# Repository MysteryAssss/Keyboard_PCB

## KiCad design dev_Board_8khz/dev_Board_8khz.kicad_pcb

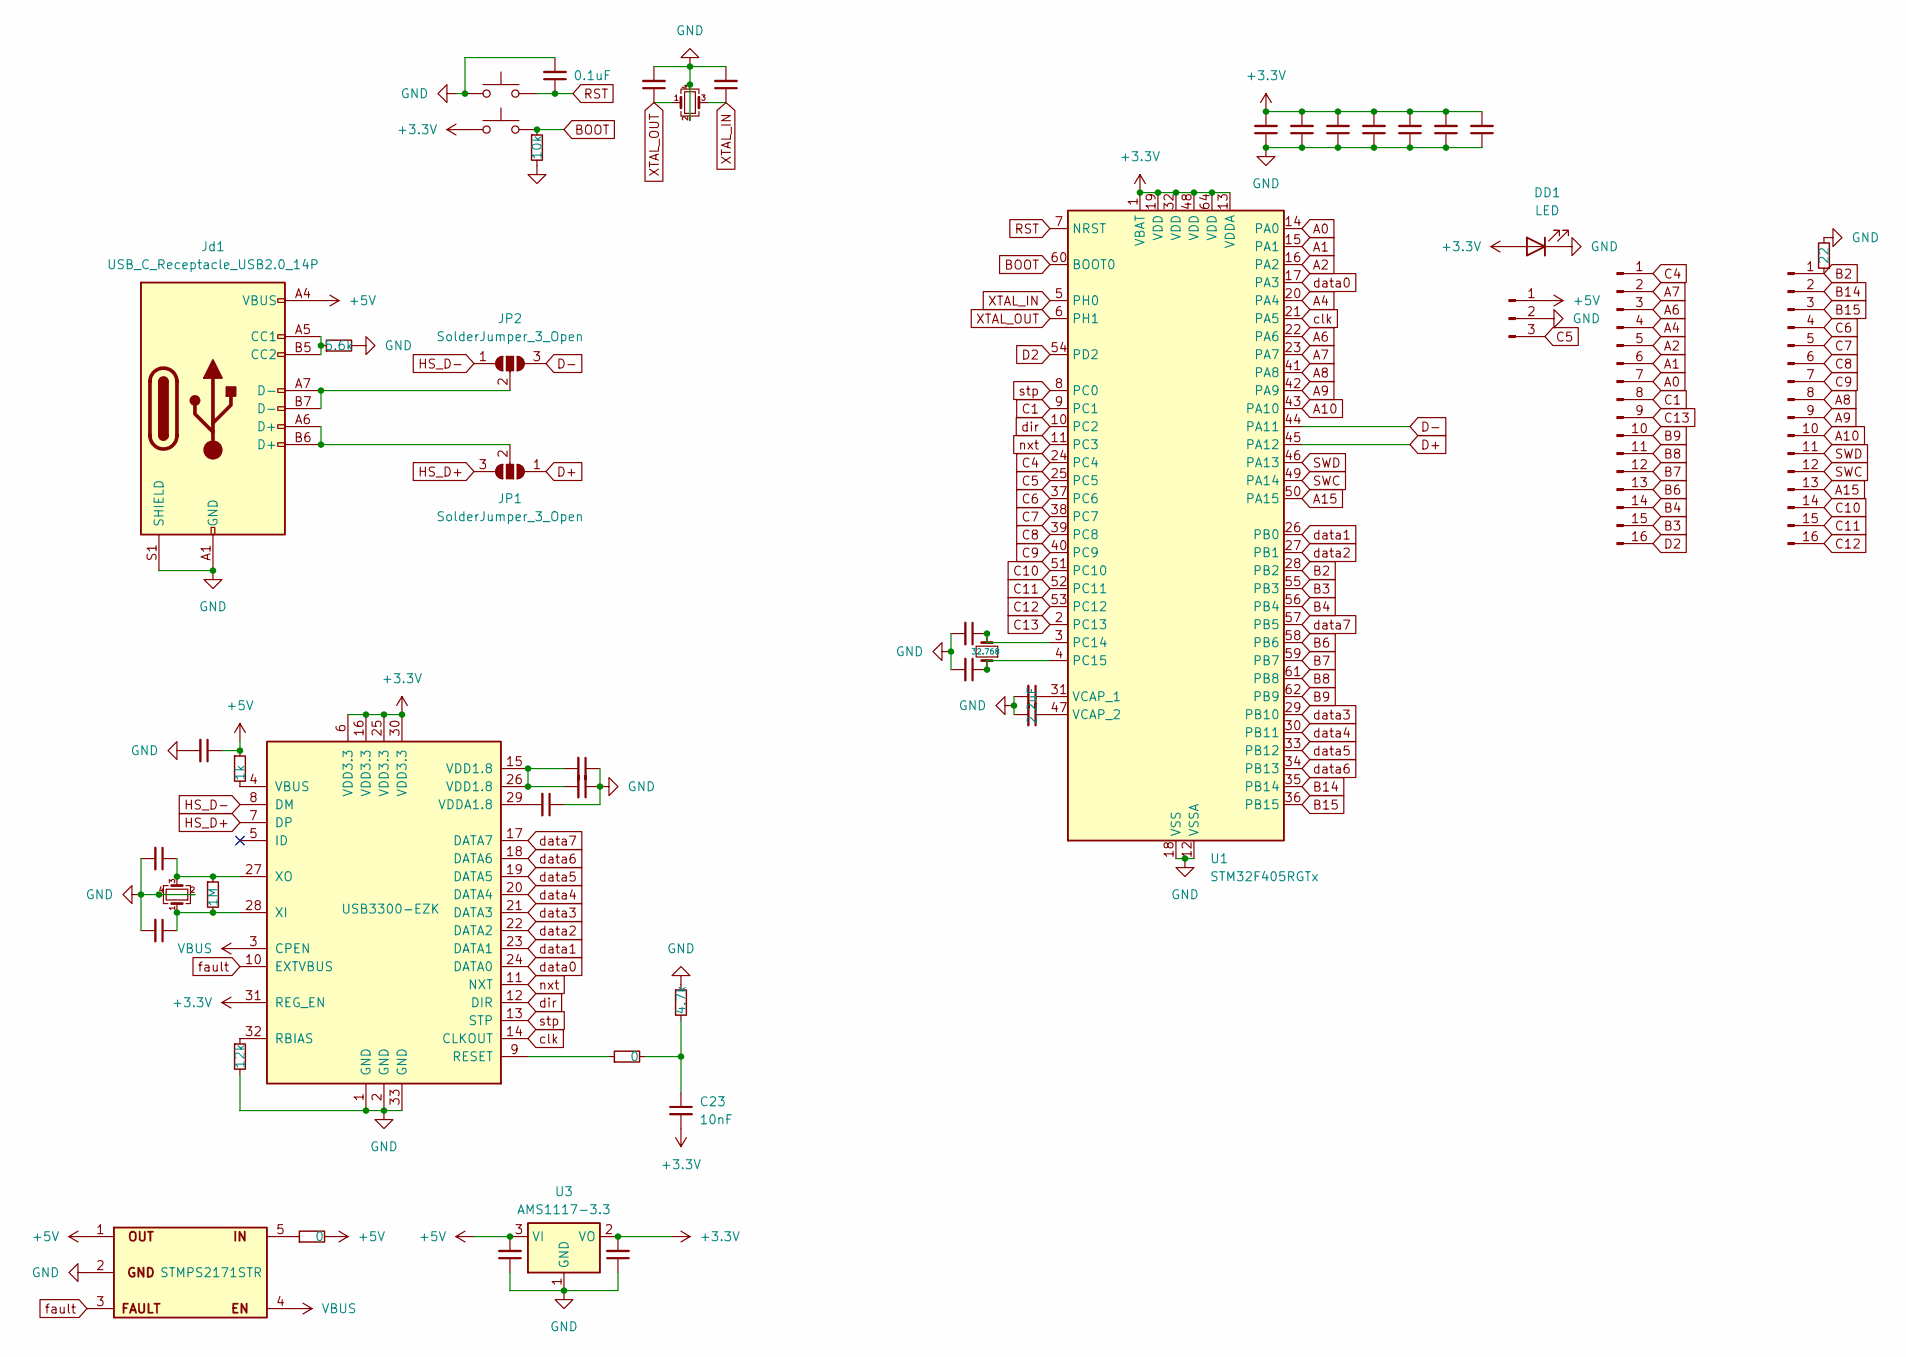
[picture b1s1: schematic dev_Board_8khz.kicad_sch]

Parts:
BOOT0: SW_Push; JST_EH_B2B-EH-A_1x02_P2.50mm_Vertical
C1: 0.1uF; C_0603_1608Metric
C2, C3: 2.2uF; C_0603_1608Metric
C4, C5, C6, C7, C8, C12, C13, C14, C15: 12pF; C_0603_1608Metric
C9, C11: 4.7uF; C_0603_1608Metric
C10: 1uF; C_0603_1608Metric
C16, C17, C18, C19, C20, C21, C22: 0.1Uf; C_0603_1608Metric
C23: 10nF; C_0603_1608Metric
DD1: LED; LED_PLCC-2_3.4x3.0mm_KA
J1: Conn_01x03_Pin; JST_EH_B3B-EH-A_1x03_P2.50mm_Vertical
J2, J3: Conn_01x16_Pin; PinHeader_1x16_P2.54mm_Vertical
J4: STMPS2171STR; SOT-23-5
JP1, JP2: SolderJumper_3_Open; SolderJumper-3_P1.3mm_Open_RoundedPad1.0x1.5mm
Jd1: USB_C_Receptacle_USB2.0_14P; USB_C_Receptacle_G-Switch_GT-USB-7010ASV
R1: 10k; R_0603_1608Metric
R2: 12k; R_0603_1608Metric
R3: 1M; R_0603_1608Metric
R4: 1k; R_0603_1608Metric
R5: 5.6k; R_0603_1608Metric
R6, R10: 0; R_0603_1608Metric
R8: 22; R_0603_1608Metric
R9: 4.7k; R_0603_1608Metric
RST1: SW_Push; JST_EH_B2B-EH-A_1x02_P2.50mm_Vertical
U1: STM32F405RGTx; LQFP-64_10x10mm_P0.5mm
U2: USB3300-EZK; QFN-32-1EP_5x5mm_P0.5mm_EP3.45x3.45mm
U3: AMS1117-3.3; SOT-223-3_TabPin2
Y1: 12mhz; Crystal_SMD_3225-4Pin_3.2x2.5mm
Y2: 24mhz; Crystal_SMD_3225-4Pin_3.2x2.5mm
Y3: 32.768; Crystal_SMD_3215-2Pin_3.2x1.5mm

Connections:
+3.3V: BOOT0.1, C13.2, C16.2, C17.2, C18.2, C19.2, C20.2, C21.2, C22.2, C23.2, DD1.2 (A), U1.1 (VBAT), U1.13 (VDDA), U1.19 (VDD), U1.32 (VDD), U1.48 (VDD), U1.64 (VDD), U2.6 (VDD3.3), U2.16 (VDD3.3), U2.25 (VDD3.3), U2.30 (VDD3.3), U2.31 (REG_EN), U3.2 (VO)
+5V: C8.1, C12.2, J1.1, J4.1, Jd1.A4 (VBUS), Jd1.A9 (VBUS), Jd1.B4 (VBUS), Jd1.B9 (VBUS), R4.1, R6.2, U3.3 (VI)
A0: J2.7, U1.14 (PA0)
A1: J2.6, U1.15 (PA1)
A2: J2.5, U1.16 (PA2)
A4: J2.4, U1.20 (PA4)
A6: J2.3, U1.22 (PA6)
A7: J2.2, U1.23 (PA7)
A8: J3.8, U1.41 (PA8)
A9: J3.9, U1.42 (PA9)
A10: J3.10, U1.43 (PA10)
A15: J3.13, U1.50 (PA15)
B2: J3.1, R8.1, U1.28 (PB2)
B3: J2.15, U1.55 (PB3)
B4: J2.14, U1.56 (PB4)
B6: J2.13, U1.58 (PB6)
B7: J2.12, U1.59 (PB7)
B8: J2.11, U1.61 (PB8)
B9: J2.10, U1.62 (PB9)
B14: J3.2, U1.35 (PB14)
B15: J3.3, U1.36 (PB15)
BOOT: BOOT0.2, R1.1, U1.60 (BOOT0)
C1: J2.8, U1.9 (PC1)
C4: J2.1, U1.24 (PC4)
C5: J1.3, U1.25 (PC5)
C6: J3.4, U1.37 (PC6)
C7: J3.5, U1.38 (PC7)
C8: J3.6, U1.39 (PC8)
C9: J3.7, U1.40 (PC9)
C10: J3.14, U1.51 (PC10)
C11: J3.15, U1.52 (PC11)
C12: J3.16, U1.53 (PC12)
C13: J2.9, U1.2 (PC13)
D2: J2.16, U1.54 (PD2)
D+: JP1.1 (A), U1.45 (PA12)
D-: JP2.3 (B), U1.44 (PA11)
GND: C1.2, C2.2, C3.2, C4.2, C5.2, C6.2, C7.2, C8.2, C9.1, C10.1, C11.1, C12.1, C13.1, C14.2, C15.2, C16.1, C17.1, C18.1, C19.1, C20.1, C21.1, C22.1, DD1.1 (K), J1.2, J4.2, Jd1.A1 (GND), Jd1.A12 (GND), Jd1.B1 (GND), Jd1.B12 (GND), Jd1.S1 (SHIELD), R1.2, R2.2, R5.2, R8.2, R9.1, RST1.1, U1.12 (VSSA), U1.18 (VSS), U1.63 (VSS), U2.1 (GND), U2.2 (GND), U2.33 (GND), U3.1 (GND), Y1.2, Y1.4, Y2.2, Y2.4
HS_D+: JP1.3 (B), U2.7 (DP)
HS_D-: JP2.1 (A), U2.8 (DM)
unnamed: C9.2, C10.2, U2.15 (VDD1.8), U2.26 (VDD1.8)
unnamed: C23.1, R9.2, R10.2
unnamed: J4.5, R6.1
unnamed: JP1.2 (C), Jd1.A6 (D+), Jd1.B6 (D+)
unnamed: JP2.2 (C), Jd1.A7 (D-), Jd1.B7 (D-)
unnamed: Jd1.A5 (CC1), Jd1.B5 (CC2), R5.1
unnamed: C15.1, U1.3 (PC14), Y3.2
unnamed: C14.1, U1.4 (PC15), Y3.1
unnamed: C2.1, U1.31 (VCAP_1)
unnamed: C3.1, U1.47 (VCAP_2)
unnamed: R2.1, U2.32 (RBIAS)
unnamed: R10.1, U2.9 (RESET)
unnamed: R4.2, U2.4 (VBUS)
unnamed: C11.2, U2.29 (VDDA1.8)
unnamed: C6.1, R3.2, U2.28 (XI), Y2.1
unnamed: C7.1, R3.1, U2.27 (XO), Y2.3
RST: C1.1, RST1.2, U1.7 (NRST)
SWC: J3.12, U1.49 (PA14)
SWD: J3.11, U1.46 (PA13)
VBUS: J4.4, U2.3 (CPEN)
XTAL_IN: C5.1, U1.5 (PH0), Y1.3
XTAL_OUT: C4.1, U1.6 (PH1), Y1.1
clk: U1.21 (PA5), U2.14 (CLKOUT)
data0: U1.17 (PA3), U2.24 (DATA0)
data1: U1.26 (PB0), U2.23 (DATA1)
data2: U1.27 (PB1), U2.22 (DATA2)
data3: U1.29 (PB10), U2.21 (DATA3)
data4: U1.30 (PB11), U2.20 (DATA4)
data5: U1.33 (PB12), U2.19 (DATA5)
data6: U1.34 (PB13), U2.18 (DATA6)
data7: U1.57 (PB5), U2.17 (DATA7)
dir: U1.10 (PC2), U2.12 (DIR)
fault: J4.3, U2.10 (EXTVBUS)
nxt: U1.11 (PC3), U2.11 (NXT)
stp: U1.8 (PC0), U2.13 (STP)

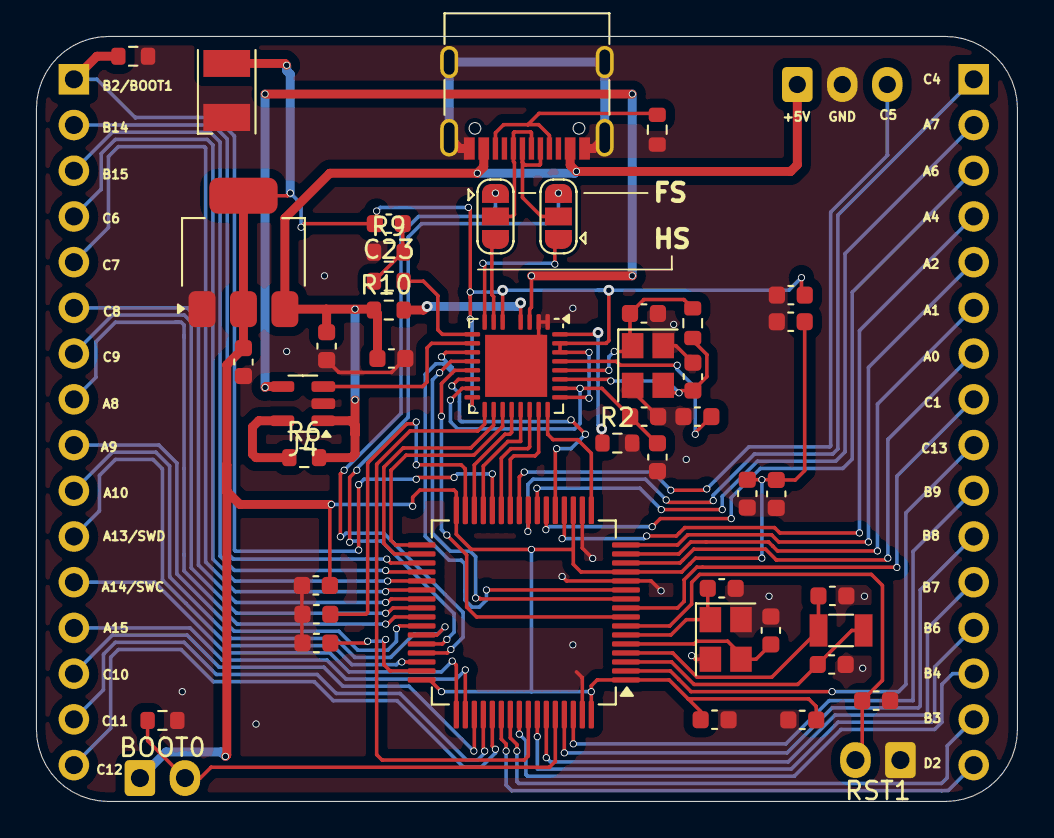
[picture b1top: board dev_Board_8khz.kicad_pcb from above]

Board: 2 copper layers, 54.5 x 42.5 mm, 48 parts (0 on the bottom side), 74 nets.

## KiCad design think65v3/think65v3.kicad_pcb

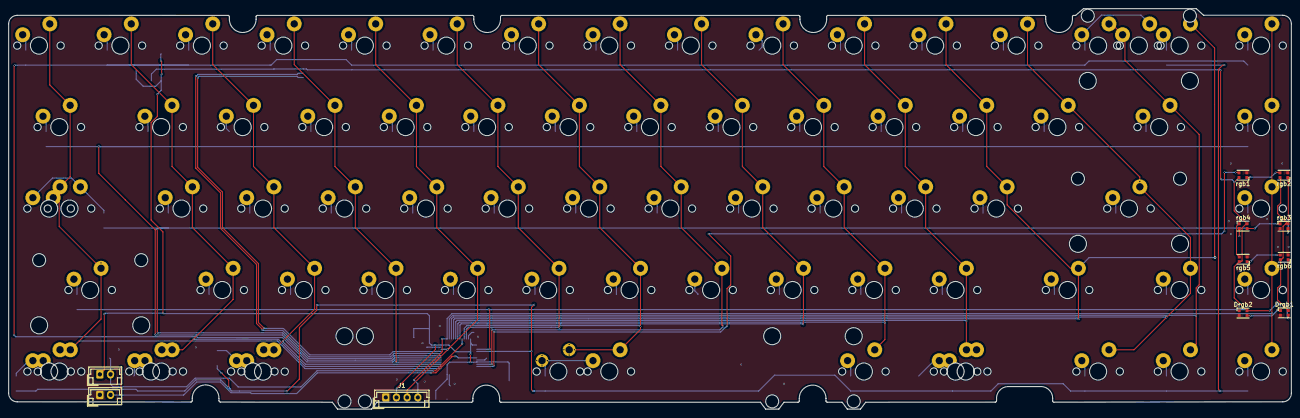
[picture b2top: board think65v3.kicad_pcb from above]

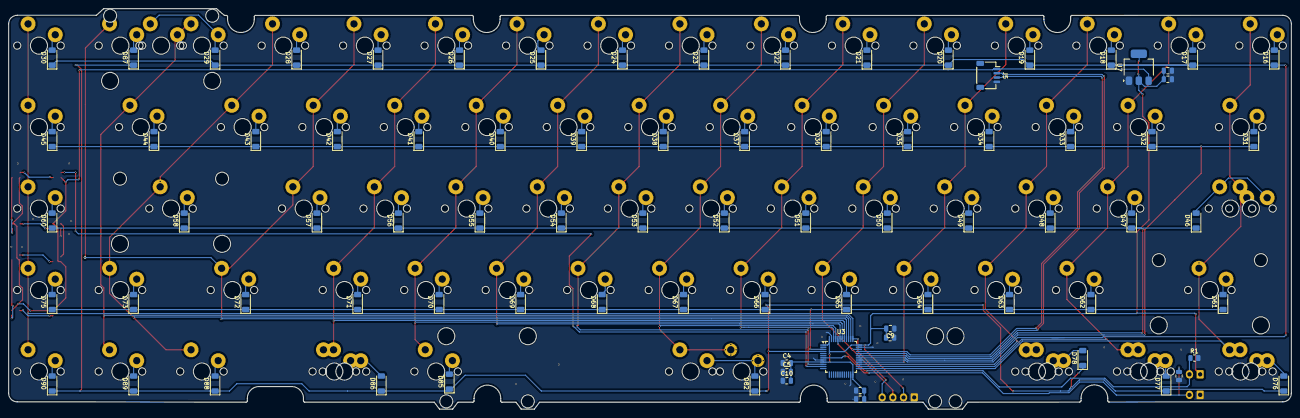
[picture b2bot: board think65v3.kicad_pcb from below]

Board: 2 copper layers, 299.9 x 93.6 mm, 168 parts (82 on the bottom side), 103 nets.

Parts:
C1, C2, C4, C5, C8, C10: 4.7uF; C_0805_2012Metric
C3, C6, C7, C9: 100nF; C_0805_2012Metric
D16, D17, D18, D19, D20, D21, D22, D23, D24, D25, D26, D27, D28, D29, D30, D31, D32, D33, D34, D35, D36, D37, D38, D39, D40, D41, D42, D43, D44, D45, D46, D47, D48, D49, D50, D51, D52, D53, D54, D55, D56, D57, D58, D60, D61, D62, D63, D64, D65, D66, D67, D68, D69, D70, D71, D72, D73, D75, D76, D77, D78, D82, D85, D86, D87, D88, D89, D90: D_Small; D_MiniMELF
Drgb1, Drgb2: WS2812B-2020; LED_WS2812B-2020_PLCC4_2.0x2.0mm
J1: Conn_01x04_Pin; JST_EH_B4B-EH-A_1x04_P2.50mm_Vertical
J5: Conn_01x04_Pin; JST_SH_SM04B-SRSS-TB_1x04-1MP_P1.00mm_Horizontal
R1: R_Small; R_0805_2012Metric
SW16, SW17, SW18, SW19, SW20, SW21, SW22, SW23, SW24, SW25, SW26, SW27, SW28, SW29, SW30, SW32, SW33, SW34, SW35, SW36, SW37, SW38, SW39, SW40, SW41, SW42, SW43, SW45, SW47, SW48, SW49, SW50, SW51, SW52, SW53, SW54, SW55, SW56, SW57, SW60, SW62, SW63, SW64, SW65, SW66, SW67, SW68, SW69, SW70, SW71, SW73, SW75, SW87, SW88, SW89, SW90, SW97: SW_Push; MXOnly-1U_N
SW31, SW44, SW96, SW98, SW101: SW_Push; MXOnly-1.5U_N
SW46, SW72: SW_Push; MXOnly-1.75U_N
SW58, SW61: SW_Push; MXOnly-2.25U_N
SW76, SW77, SW78, SW85, SW86, SW100: SW_Push; MXOnly-1.25U_N
SW82: SW_Push; MXOnly-6.25U-FLIPPED-ReversedStabilizers_N
SW99: SW_Push; MXOnly-7U-ReversedStabilizers_N
SW1001: SW_Push; MXOnly-2U_N
SWbôt1: SW_Push; JST_EH_B2B-EH-A_1x02_P2.50mm_Vertical
SWbôtrst1: SW_Push; JST_EH_B2B-EH-A_1x02_P2.50mm_Vertical
U3: STM32F072-LQFP48; LQFP-48_7x7mm_P0.5mm
U7: AMS1117; SOT-223-3_TabPin2
rgb1, rgb2, rgb3, rgb4, rgb5, rgb6: WS2812B-2020; LED_WS2812B-2020_PLCC4_2.0x2.0mm

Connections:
+3.3V: C2.2, C3.2, C4.2, C5.2, C6.2, C7.2, C8.2, C9.2, C10.2, J1.2, SWbôt1.1, U3.1 (VBAT), U3.9 (VDDA), U3.24 (VDD), U3.36 (VDDIO2), U3.48 (VDD), U7.2 (VO)
+5V: Drgb1.4 (VDD), Drgb2.4 (VDD), J5.1, U7.3 (VI), rgb1.4 (VDD), rgb2.4 (VDD), rgb3.4 (VDD), rgb4.4 (VDD), rgb5.4 (VDD), rgb6.4 (VDD)
C0: SW16.2, SW31.2, SW46.1, SW61.2, SW76.2, SW96.2, SW100.2, U3.25 (PB12)
C1: SW17.2, SW32.2, SW47.2, SW62.2, SW77.2, SW97.2, U3.26 (SPI2_SCK/I2S2_CK/I2C2_SCL/PB13)
C2: SW18.2, SW33.2, SW48.2, SW63.2, SW78.2, SW98.2, U3.27 (PB14/SPI2_MISO/I2S2_MCK/I2C2_SDA/TIM15_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)
C3: SW19.2, SW34.2, SW49.2, SW64.2, U3.28 (SPI2_MOSI/I2S2_SD/PB15)
C4: J1.3, SW20.2, SW35.2, SW50.2, SW65.2, U3.34 (SWDIO/PA13)
C5: SW21.2, SW36.2, SW51.2, SW66.2, U3.46 (SPI2_NSS/I2S2_WS/I2C1_SDA/TIM17_CH1/PB9)
C6: SW22.2, SW37.2, SW52.2, SW67.2, SW82.2, SW99.2, U3.45 (I2C1_SCL/TIM16_CH1/PB8)
C7: SW23.2, SW38.2, SW53.2, SW68.2, U3.10 (PA0/ADC_IN0)
C8: SW24.2, SW39.2, SW54.2, SW69.2, U3.43 (2C1_SDA/PB7)
C9: SW25.2, SW40.2, SW55.2, SW70.2, SW85.2, U3.42 (I2C1_SCL/PB6)
C10: SW26.2, SW41.2, SW56.2, SW71.2, SW86.2, SW101.2, U3.41 (SPI1_MOSI/I2S1_SD/TIM3_CH2/PB5)
C11: SW27.2, SW42.2, SW57.2, SW72.2, SW87.2, U3.40 (SPI1_MISO/I2S1_MCK/TIM3_CH1/PB4)
C12: SW28.2, SW43.2, SW58.2, SW73.2, SW88.2, U3.39 (SPI1_SCK/I2S1_CK/TIM2_CH2/PB3)
C13: SW29.2, SW44.2, SW89.2, SW1001.1, U3.38 (PA2)
C14: J1.4, SW30.2, SW45.2, SW60.2, SW75.2, SW90.2, U3.37 (SWCLK/PA14)
D+: J5.3, U3.33 (USB_DP/PA12)
D-: J5.2, U3.32 (USB_DM/TIM1_CH4/PA11)
GND: C1.2, C2.1, C3.1, C4.1, C5.1, C6.1, C7.1, C8.1, C9.1, C10.1, Drgb1.2 (VSS), Drgb2.2 (VSS), J1.1, J5.4, R1.2, SWbôtrst1.1, U3.8 (VSSA), U3.23 (VSS), U3.35 (VSS), U3.47 (VSS), U7.1 (ADJ), rgb1.2 (VSS), rgb2.2 (VSS), rgb3.2 (VSS), rgb4.2 (VSS), rgb5.2 (VSS), rgb6.2 (VSS)
unnamed: D16.2 (A), SW16.1
unnamed: D17.2 (A), SW17.1
unnamed: D18.2 (A), SW18.1
unnamed: D19.2 (A), SW19.1
unnamed: D20.2 (A), SW20.1
unnamed: D21.2 (A), SW21.1
unnamed: D22.2 (A), SW22.1
unnamed: D23.2 (A), SW23.1
unnamed: D24.2 (A), SW24.1
unnamed: D25.2 (A), SW25.1
unnamed: D26.2 (A), SW26.1
unnamed: D27.2 (A), SW27.1
unnamed: D28.2 (A), SW28.1
unnamed: D29.2 (A), SW29.1, SW1001.2
unnamed: D30.2 (A), SW30.1
unnamed: D31.2 (A), SW31.1
unnamed: D32.2 (A), SW32.1
unnamed: D33.2 (A), SW33.1
unnamed: D34.2 (A), SW34.1
unnamed: D35.2 (A), SW35.1
unnamed: D36.2 (A), SW36.1
unnamed: D37.2 (A), SW37.1
unnamed: D38.2 (A), SW38.1
unnamed: D39.2 (A), SW39.1
unnamed: D40.2 (A), SW40.1
unnamed: D41.2 (A), SW41.1
unnamed: D42.2 (A), SW42.1
unnamed: D43.2 (A), SW43.1
unnamed: D44.2 (A), SW44.1
unnamed: D45.2 (A), SW45.1
unnamed: D46.2 (A), SW46.2, SW100.1
unnamed: D47.2 (A), SW47.1
unnamed: D48.2 (A), SW48.1
unnamed: D49.2 (A), SW49.1
unnamed: D50.2 (A), SW50.1
unnamed: D51.2 (A), SW51.1
unnamed: D52.2 (A), SW52.1
unnamed: D53.2 (A), SW53.1
unnamed: D54.2 (A), SW54.1
unnamed: D55.2 (A), SW55.1
unnamed: D56.2 (A), SW56.1
unnamed: D57.2 (A), SW57.1
unnamed: D58.2 (A), SW58.1
unnamed: D60.2 (A), SW60.1
unnamed: D61.2 (A), SW61.1
unnamed: D62.2 (A), SW62.1
unnamed: D63.2 (A), SW63.1
unnamed: D64.2 (A), SW64.1
unnamed: D65.2 (A), SW65.1
unnamed: D66.2 (A), SW66.1
unnamed: D67.2 (A), SW67.1
unnamed: D68.2 (A), SW68.1
unnamed: D69.2 (A), SW69.1
unnamed: D70.2 (A), SW70.1
unnamed: D71.2 (A), SW71.1
unnamed: D72.2 (A), SW72.1
unnamed: D73.2 (A), SW73.1
unnamed: D75.2 (A), SW75.1
unnamed: D76.2 (A), SW76.1, SW96.1
unnamed: D77.2 (A), SW77.1, SW97.1
unnamed: D78.2 (A), SW78.1, SW98.1
unnamed: D82.2 (A), SW82.1, SW99.1
unnamed: D85.2 (A), SW85.1
unnamed: D86.2 (A), SW86.1, SW101.1
unnamed: D87.2 (A), SW87.1
unnamed: D88.2 (A), SW88.1
unnamed: D89.2 (A), SW89.1
unnamed: D90.2 (A), SW90.1
unnamed: Drgb1.3 (DIN), rgb6.1 (DOUT)
unnamed: Drgb1.1 (DOUT), Drgb2.3 (DIN)
unnamed: rgb1.1 (DOUT), rgb2.3 (DIN)
unnamed: rgb2.1 (DOUT), rgb3.3 (DIN)
unnamed: rgb3.1 (DOUT), rgb4.3 (DIN)
unnamed: rgb4.1 (DOUT), rgb5.3 (DIN)
unnamed: rgb5.1 (DOUT), rgb6.3 (DIN)
R1: D16.1 (K), D17.1 (K), D18.1 (K), D19.1 (K), D20.1 (K), D21.1 (K), D22.1 (K), D23.1 (K), D24.1 (K), D25.1 (K), D26.1 (K), D27.1 (K), D28.1 (K), D29.1 (K), D30.1 (K), U3.29 (TIM1_CH1/PA8)
R2: D31.1 (K), D32.1 (K), D33.1 (K), D34.1 (K), D35.1 (K), D36.1 (K), D37.1 (K), D38.1 (K), D39.1 (K), D40.1 (K), D41.1 (K), D42.1 (K), D43.1 (K), D44.1 (K), D45.1 (K), U3.30 (TIM1_CH2/PA9)
R3: D46.1 (K), D47.1 (K), D48.1 (K), D49.1 (K), D50.1 (K), D51.1 (K), D52.1 (K), D53.1 (K), D54.1 (K), D55.1 (K), D56.1 (K), D57.1 (K), D58.1 (K), D60.1 (K), U3.31 (TIM1_CH3/PA10)
R4: D61.1 (K), D62.1 (K), D63.1 (K), D64.1 (K), D65.1 (K), D66.1 (K), D67.1 (K), D68.1 (K), D69.1 (K), D70.1 (K), D71.1 (K), D72.1 (K), D73.1 (K), D75.1 (K), U3.3 (PC14/OSC32_IN)
R5: D76.1 (K), D77.1 (K), D78.1 (K), D82.1 (K), D85.1 (K), D86.1 (K), D87.1 (K), D88.1 (K), D89.1 (K), D90.1 (K), U3.4 (PC15/OSC32_OUT)
RGB: U3.11 (PA1/ADC_IN1), rgb1.3 (DIN)
RST: C1.1, SWbôtrst1.2, U3.7 (NRST)
boot: R1.1, SWbôt1.2, U3.44 (BOOT0)

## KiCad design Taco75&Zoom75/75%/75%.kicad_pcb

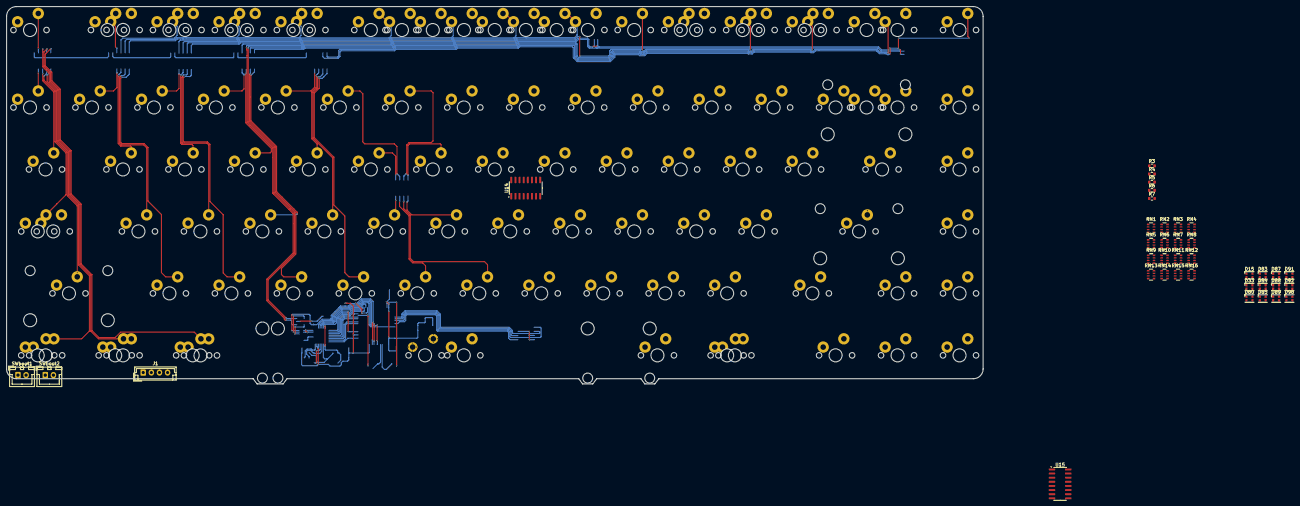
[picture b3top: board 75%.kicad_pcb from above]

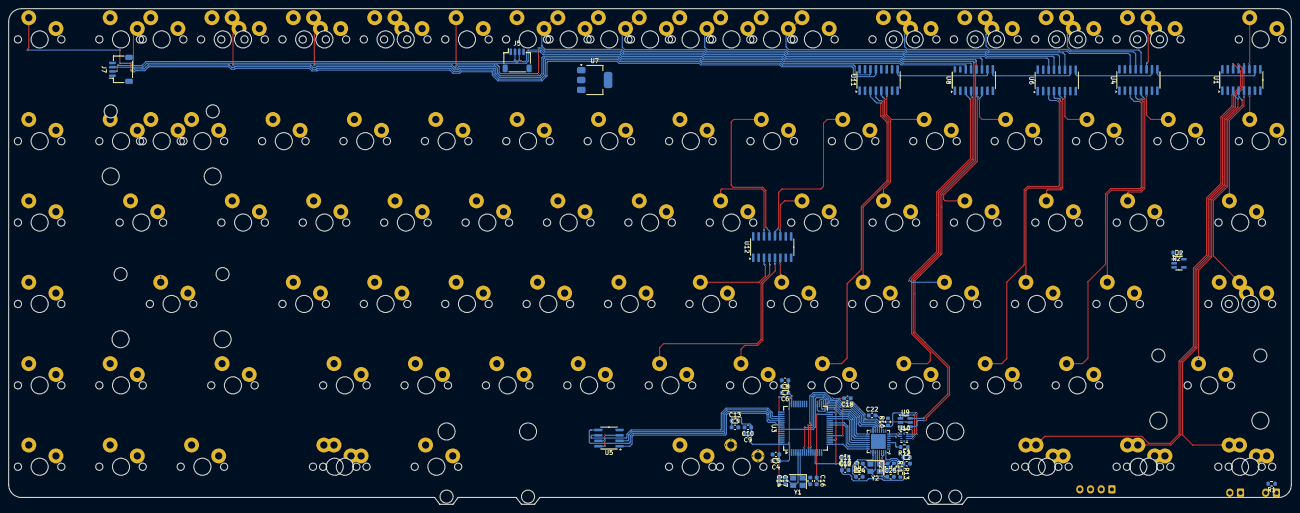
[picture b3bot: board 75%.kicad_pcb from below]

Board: 2 copper layers, 300.2 x 116.0 mm, 188 parts (48 on the bottom side), 115 nets.

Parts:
C1, C2, C3, C4, C5, C6, C8, C10, C12: 0.1uF; C_0603_1608Metric
C7, C9, C11, C13, C18, C19, C22, C23, C24, C25: 1uF; C_0603_1608Metric
C14, C15, C20, C21: 9pf; C_0603_1608Metric
C16, C17: 2.2uF; C_0603_1608Metric
D15, D33, D80, D83, D84, D85, D87, D88, D89, D91, D92, D98: WS2812B-2020; LED_WS2812B-2020_PLCC4_2.0x2.0mm
J1: Conn_01x04_Pin; JST_EH_B4B-EH-A_1x04_P2.50mm_Vertical
J5, J7: Conn_01x04_Pin; JST_SH_SM04B-SRSS-TB_1x04-1MP_P1.00mm_Horizontal
R1, R2, R3, R10: 10k; R_0603_1608Metric
R4, R5, R6, R7: 0; R_0603_1608Metric
R11, R12, R13: 1k; R_0603_1608Metric
RN1, RN2, RN3, RN4, RN5, RN6, RN7, RN8, RN9, RN10, RN11, RN12, RN13, RN14, RN15, RN16: R_Pack04; R_Array_Convex_4x0603
SW1, SW2, SW3, SW4, SW5, SW6, SW7, SW8, SW9, SW10, SW11, SW12, SW13, SW14, SW15, SW16, SW17, SW18, SW19, SW20, SW21, SW22, SW23, SW24, SW25, SW26, SW27, SW28, SW29, SW30, SW32, SW33, SW34, SW35, SW36, SW37, SW38, SW39, SW40, SW41, SW42, SW43, SW45, SW47, SW48, SW49, SW50, SW51, SW52, SW53, SW54, SW55, SW56, SW57, SW59, SW60, SW62, SW63, SW64, SW65, SW66, SW67, SW68, SW69, SW70, SW71, SW73, SW74, SW75, SW79, SW80, SW81, SW83, SW84, SW87, SW88, SW89, SW90, SW91, SW92, SW93, SW94, SW95, SW97: SW_Push; MXOnly-1U_N
SW31, SW44, SW96, SW98, SW101: SW_Push; MXOnly-1.5U_N
SW46, SW72: SW_Push; MXOnly-1.75U_N
SW58, SW61: SW_Push; MXOnly-2.25U_N
SW76, SW77, SW78, SW85, SW86, SW100: SW_Push; MXOnly-1.25U_N
SW82: SW_Push; MXOnly-6.25U-FLIPPED-ReversedStabilizers_N
SW99: SW_Push; MXOnly-7U-ReversedStabilizers_N
SW1001: SW_Push; MXOnly-2U_N
SWboot1, SWboot2: SW_Push; JST_XH_B2B-XH-A_1x02_P2.50mm_Vertical
U1, U4, U6, U8, U11, U12, U14, U15: 74HC165; SOP-16_3.9x9.9mm_P1.27mm
U2: SN74LVC1G125DBV; SOT-23-5
U3: STM32F405RGTx; LQFP-64_10x10mm_P0.5mm
U5: MB85RS16; SOIC-8_3.9x4.9mm_P1.27mm
U7: AMS1117; SOT-223-3_TabPin2
U9: USBLC6-2SC6; SOT-23-6
U10: TS3USB221RSER; Texas_UQFN-10_1.5x2mm_P0.5mm
U13: USB3300-EZK; QFN-32-1EP_5x5mm_P0.5mm_EP3.45x3.45mm
Y1: Crystal_GND24_Small; Crystal_SMD_3225-4Pin_3.2x2.5mm
Y2: 24mhz; Crystal_SMD_3225-4Pin_3.2x2.5mm

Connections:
1: SW17.2, U4.6 (D7)
2: SW18.2, U6.6 (D7)
3: SW19.2, U8.6 (D7)
4: SW20.2, U11.6 (D7)
5: SW21.2, U12.12 (D1)
6: SW22.2, U12.13 (D2)
165_CS: R2.2, U2.1, U3.58 (PB6)
+3.3V: C1.1, C2.1, C3.1, C4.1, C5.1, C6.1, C7.1, C8.1, C9.1, C10.1, C11.1, C12.1, C13.1, C18.2, C19.2, J1.2, R2.1, RN1.1 (R1.1), RN1.2 (R2.1), RN1.3 (R3.1), RN1.4 (R4.1), RN2.1 (R1.1), RN2.2 (R2.1), RN2.3 (R3.1), RN2.4 (R4.1), RN3.1 (R1.1), RN3.2 (R2.1), RN3.3 (R3.1), RN3.4 (R4.1), RN4.1 (R1.1), RN4.2 (R2.1), RN4.3 (R3.1), RN4.4 (R4.1), RN5.1 (R1.1), RN5.2 (R2.1), RN5.3 (R3.1), RN5.4 (R4.1), RN6.1 (R1.1), RN6.2 (R2.1), RN6.3 (R3.1), RN6.4 (R4.1), RN7.1 (R1.1), RN7.2 (R2.1), RN7.3 (R3.1), RN7.4 (R4.1), RN8.1 (R1.1), RN8.2 (R2.1), RN8.3 (R3.1), RN8.4 (R4.1), RN9.1 (R1.1), RN9.2 (R2.1), RN9.3 (R3.1), RN9.4 (R4.1), RN10.1 (R1.1), RN10.2 (R2.1), RN10.3 (R3.1), RN10.4 (R4.1), RN11.1 (R1.1), RN11.2 (R2.1), RN11.3 (R3.1), RN11.4 (R4.1), RN12.1 (R1.1), RN12.2 (R2.1), RN12.3 (R3.1), RN12.4 (R4.1), RN13.1 (R1.1), RN13.2 (R2.1), RN13.3 (R3.1), RN13.4 (R4.1), RN14.1 (R1.1), RN14.2 (R2.1), RN14.3 (R3.1), RN14.4 (R4.1), RN15.1 (R1.1), RN15.2 (R2.1), RN15.3 (R3.1), RN15.4 (R4.1), RN16.1 (R1.1), RN16.2 (R2.1), RN16.3 (R3.1), RN16.4 (R4.1), SWboot1.1, U1.16 (VCC), U2.5 (VCC), U3.1 (VBAT), U3.13 (VDDA), U3.19 (VDD), U3.32 (VDD), U3.48 (VDD), U3.64 (VDD), U4.16 (VCC), U5.3 (~WP), U5.7 (~HOLD), U5.8 (VDD), U6.16 (VCC), U7.2 (VO), U8.16 (VCC), U10.10 (VCC), U11.16 (VCC), U12.16 (VCC), U13.6 (VDD3.3), U13.16 (VDD3.3), U13.25 (VDD3.3), U13.30 (VDD3.3), U13.31 (REG_EN), U14.16 (VCC), U15.16 (VCC)
+5V: C22.2, D15.4 (VDD), D33.4 (VDD), D80.4 (VDD), D83.4 (VDD), D84.4 (VDD), D85.4 (VDD), D87.4 (VDD), D88.4 (VDD), D89.4 (VDD), D91.4 (VDD), D92.4 (VDD), D98.4 (VDD), J5.1, J7.1, R12.1, U7.3 (VI), U9.5 (VBUS)
CLK: U3.21 (PA5), U13.14 (CLKOUT)
D+_FS: U3.45 (PA12), U10.3 (2D+)
D-_FS: U3.44 (PA11), U10.4 (2D-)
DIR: U3.10 (PC2), U13.12 (DIR)
Data0: U3.17 (PA3), U13.24 (DATA0)
Data1: U3.26 (PB0), U13.23 (DATA1)
Data2: U3.27 (PB1), U13.22 (DATA2)
Data3: U3.29 (PB10), U13.21 (DATA3)
Data4: U3.30 (PB11), U13.20 (DATA4)
Data5: U3.33 (PB12), U13.19 (DATA5)
Data6: U3.34 (PB13), U13.18 (DATA6)
Data7: U3.57 (PB5), U13.17 (DATA7)
EEPROM: U3.55 (PB3), U5.1 (~CS)
GND: C1.2, C2.2, C3.2, C4.2, C5.2, C6.2, C7.2, C8.2, C9.2, C10.2, C11.2, C12.2, C13.2, C14.1, C15.1, C16.2, C17.2, C18.1, C19.1, C20.1, C21.1, C22.1, C23.2, C24.2, C25.2, D15.2 (VSS), D33.2 (VSS), D80.2 (VSS), D83.2 (VSS), D84.2 (VSS), D85.2 (VSS), D87.2 (VSS), D88.2 (VSS), D89.2 (VSS), D91.2 (VSS), D92.2 (VSS), D98.2 (VSS), J1.1, J5.4, J7.4, R1.1, R4.1, R5.1, R6.1, R7.1, R10.2, R13.2, SWboot2.1, U1.8 (GND), U1.15 (~CE), U2.3 (GND), U3.12 (VSSA), U3.18 (VSS), U3.63 (VSS), U4.8 (GND), U4.15 (~CE), U5.4 (GND), U6.8 (GND), U6.15 (~CE), U7.1 (ADJ), U8.8 (GND), U8.15 (~CE), U9.2 (GND), U10.5 (GND), U10.6 (OE), U11.8 (GND), U11.15 (~CE), U12.8 (GND), U12.15 (~CE), U13.1 (GND), U13.2 (GND), U13.9 (RESET), U13.33 (GND), U14.8 (GND), U14.15 (~CE), U15.8 (GND), U15.15 (~CE), Y1.2, Y1.4, Y2.2, Y2.4
GND1: R4.2, R5.2, R6.2, R7.2, SW1.1, SW2.1, SW3.1, SW4.1, SW5.1, SW6.1, SW7.1, SW8.1, SW9.1, SW10.1, SW11.2, SW12.2, SW13.2, SW14.2, SW15.1, SW16.1, SW17.1, SW18.1, SW19.1, SW20.1, SW21.1, SW22.1, SW23.1, SW24.1, SW25.1, SW26.1, SW27.1, SW28.1, SW29.1, SW30.1, SW31.1, SW32.1, SW33.1, SW34.1, SW35.1, SW36.1, SW37.1, SW38.1, SW39.1, SW40.1, SW41.1, SW42.1, SW43.1, SW44.1, SW45.1, SW46.2, SW47.1, SW48.1, SW49.1, SW50.1, SW51.1, SW52.1, SW53.1, SW54.1, SW55.1, SW56.1, SW57.1, SW58.1, SW59.2, SW60.1, SW61.1, SW62.1, SW63.1, SW64.1, SW65.1, SW66.1, SW67.1, SW68.1, SW69.1, SW70.1, SW71.1, SW72.1, SW73.1, SW74.2, SW75.1, SW76.1, SW77.1, SW78.1, SW79.2, SW80.2, SW81.2, SW82.1, SW83.2, SW84.2, SW85.1, SW86.1, SW87.1, SW88.1, SW89.1, SW90.1, SW91.2, SW92.1, SW93.1, SW94.1, SW95.1, SW96.1, SW97.1, SW98.1, SW99.1, SW100.1, SW101.1, SW1001.2
LATCH: U1.1 (~PL), U3.59 (PB7), U4.1 (~PL), U6.1 (~PL), U8.1 (~PL), U11.1 (~PL), U12.1 (~PL), U14.1 (~PL), U15.1 (~PL)
L_Ctrl: SW76.2, SW96.2, U1.12 (D1)
L_S: SW61.2, U1.3 (D4)
L_Win: SW77.2, SW97.2, U1.13 (D2)
L_alt: SW78.2, SW98.2, U1.14 (D3)
M0: SW15.2, U11.13 (D2)
MISO: U2.4, U3.52 (PC11), U5.2 (SO)
MOSI: U3.53 (PC12), U5.5 (SI)
NXT: U3.11 (PC3), U13.11 (NXT)
unnamed: C23.1, C24.1, U13.15 (VDD1.8), U13.26 (VDD1.8)
unnamed: D15.3 (DIN), D33.1 (DOUT)
unnamed: D15.1 (DOUT), D80.3 (DIN)
unnamed: D33.3 (DIN), D88.1 (DOUT)
unnamed: D80.1 (DOUT), D89.3 (DIN)
unnamed: D83.1 (DOUT), D84.3 (DIN)
unnamed: D84.1 (DOUT), D85.3 (DIN)
unnamed: D85.1 (DOUT), D87.3 (DIN)
unnamed: D87.1 (DOUT), D88.3 (DIN)
unnamed: D89.1 (DOUT), D91.3 (DIN)
unnamed: D91.1 (DOUT), D92.3 (DIN)
unnamed: D92.1 (DOUT), D98.3 (DIN)
unnamed: J5.2, J7.2, U9.4 (I/O2)
unnamed: J5.3, J7.3, U9.6 (I/O1)
unnamed: U1.10 (DS), U4.9 (Q7)
unnamed: R1.2, SWboot1.2, U3.60 (BOOT0)
unnamed: R3.2, U3.40 (PC9)
unnamed: C14.2, U3.5 (PH0), Y1.3
unnamed: C15.2, U3.6 (PH1), Y1.1
unnamed: C16.1, U3.31 (VCAP_1)
unnamed: C17.1, U3.47 (VCAP_2)
unnamed: U4.10 (DS), U6.9 (Q7)
unnamed: U6.10 (DS), U8.9 (Q7)
unnamed: U10.1 (1D+), U13.7 (DP)
unnamed: U10.2 (1D-), U13.8 (DM)
unnamed: U9.1 (I/O1), U10.8 (D+)
unnamed: U9.3 (I/O2), U10.7 (D-)
unnamed: U11.10 (DS), U12.9 (Q7)
unnamed: U8.10 (DS), U11.9 (Q7)
unnamed: U12.10 (DS), U14.9 (Q7)
unnamed: R13.1, U13.32 (RBIAS)
unnamed: R12.2, U13.4 (VBUS)
unnamed: C25.1, U13.29 (VDDA1.8)
unnamed: C21.2, R11.2, U13.28 (XI), Y2.1
unnamed: C20.2, R11.1, U13.27 (XO), Y2.3
unnamed: U14.10 (DS), U15.9 (Q7)
RGB: D83.3 (DIN), R3.1
RST: SWboot2.2, U3.7 (NRST)
R_alt: SW86.2, SW101.2
SCK: U1.2 (CP), U3.51 (PC10), U4.2 (CP), U5.6 (SCK), U6.2 (CP), U8.2 (CP), U11.2 (CP), U12.2 (CP), U14.2 (CP), U15.2 (CP)
SR_DOUT: U1.9 (Q7), U2.2
STP: U3.8 (PC0), U13.13 (STP)
SWC: J1.4, U3.49 (PA14)
SWD: J1.3, U3.46 (PA13)
USB_MUX: R10.1, U3.35 (PB14), U10.9 (S)
`: SW16.2, U1.6 (D7)
a: SW47.2, U4.4 (D5)
b: SW66.2, U12.5 (D6)
bckspc: SW29.2, SW1001.1
c: SW64.2, U8.4 (D5)
cap: SW46.1, SW100.2, U1.4 (D5)
d: SW49.2, U8.3 (D4)
e: SW34.2, U8.5 (D6)
esc: SW1.2, U1.11 (D0)
f: SW50.2, U11.4 (D5)
f1: SW2.2, SW59.1, U4.11 (D0)
f2: SW3.2, SW74.1, U4.12 (D1)
f3: SW4.2, SW79.1, U4.13 (D2)
f4: SW5.2, SW80.1, U4.14 (D3)
f5: SW6.2, SW81.1, U6.11 (D0)
f6: SW7.2, SW83.1, U6.12 (D1)
f7: SW8.2, SW84.1, U6.13 (D2)
f8: SW9.2, SW91.1, U6.14 (D3)
f9: SW10.2, U8.11 (D0)
f10: SW11.1, SW92.2, U8.12 (D1)
f11: SW12.1, SW93.2, U8.13 (D2)
f12: SW13.1, SW94.2, U8.14 (D3)
f13: SW14.1, SW95.2, U11.14 (D3)
g: SW51.2, U12.6 (D7)
h: SW52.2, U12.3 (D4)
n: SW67.2, U12.4 (D5)
q: SW32.2, U4.5 (D6)
r: SW35.2, U11.5 (D6)
s: SW48.2, U6.4 (D5)
space: SW82.2, SW99.2
t: SW36.2, U12.11 (D0)
tab: SW31.2, U1.5 (D6)
v: SW65.2, U11.3 (D4)
w: SW33.2, U6.5 (D6)
x: SW63.2, U6.3 (D4)
y: SW37.2, U12.14 (D3)
z: SW62.2, U4.3 (D4)
